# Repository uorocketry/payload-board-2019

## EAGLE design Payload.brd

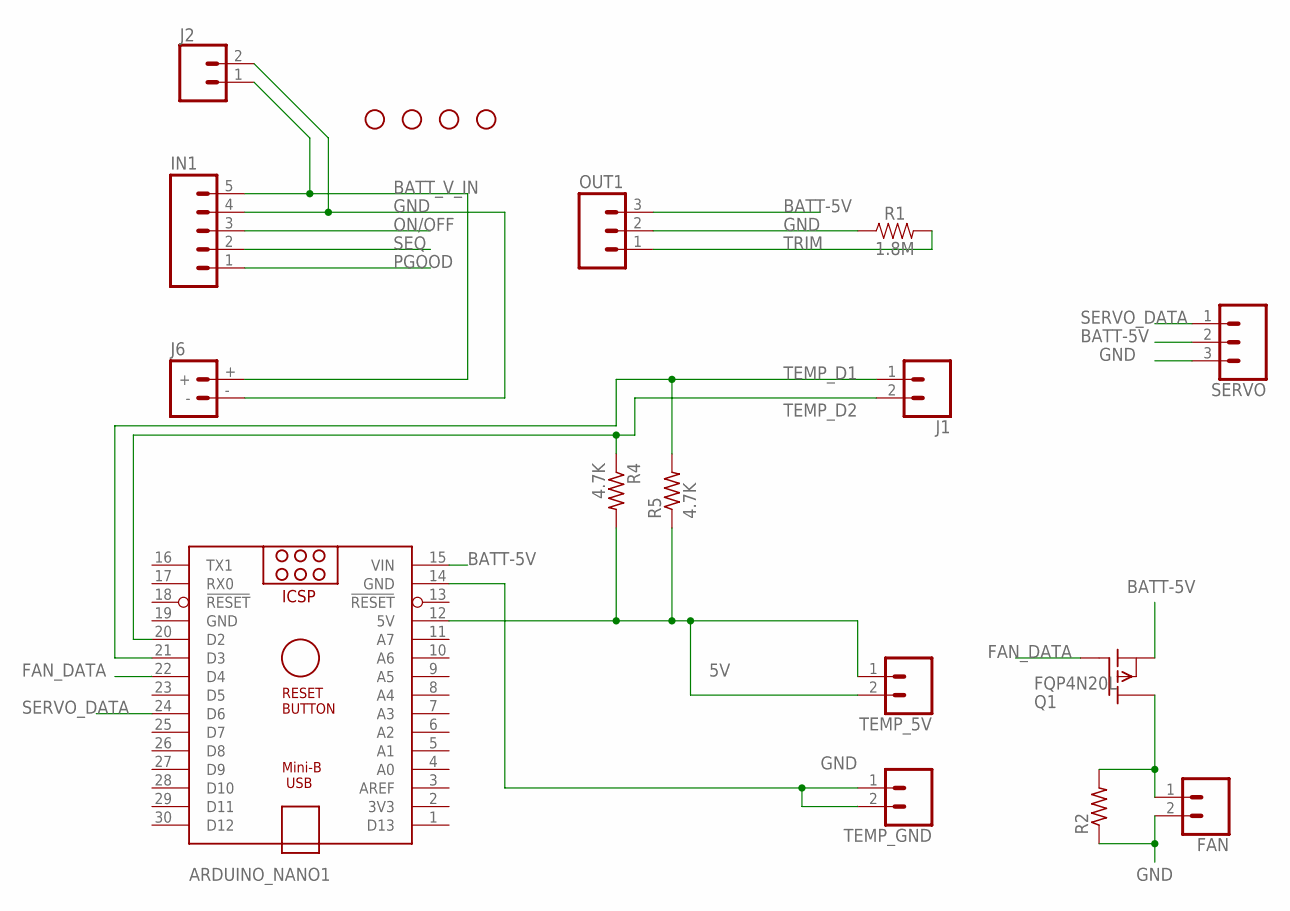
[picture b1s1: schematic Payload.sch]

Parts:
ARDUINO_NANO1: ARDUINO_NANO
FAN: CONN_023.5MM; SCREWTERMINAL-3.5MM-2
IN1: M05PTH; 1X05
J1, J2: CONN_023.5MM; SCREWTERMINAL-3.5MM-2
J6: BATTERY_CONN_DEANS; DEANS
OUT1: M03PTH; 1X03
Q1: FQP4N20L; TO220
R1: 1.8M; 0603
R2: R-US_0207/10; 0207/10
R4, R5: 4.7K; 0207/10
SERVO: CONN_03; 1X03
TEMP_5V: CONN_023.5MM; SCREWTERMINAL-3.5MM-2
TEMP_GND: CONN_023.5MM; SCREWTERMINAL-3.5MM-2
U$2, U$6, U$7, U$8: STAND-OFF

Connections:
5V: ARDUINO_NANO1.12 (5V), R4.2, R5.1, TEMP_5V.1, TEMP_5V.2
BATT-5V: ARDUINO_NANO1.15 (VIN), OUT1.3, Q1.3 (S), SERVO.2
BATT_V_IN: IN1.5, J2.1, J6.+
FAN_DATA: ARDUINO_NANO1.22 (D4), Q1.1 (G)
GND: ARDUINO_NANO1.14 (GND), ARDUINO_NANO1.19 (GND), FAN.2, IN1.4, J2.2, J6.-, OUT1.2, R1.1, R2.1, SERVO.3, TEMP_GND.1, TEMP_GND.2
unnamed: FAN.1, Q1.2 (D), R2.2
ON/OFF: IN1.3
PGOOD: IN1.1
SEQ: IN1.2
SERVO_DATA: ARDUINO_NANO1.24 (D6), SERVO.1
TEMP_D1: ARDUINO_NANO1.21 (D3), J1.1, R5.2
TEMP_D2: ARDUINO_NANO1.20 (D2), J1.2, R4.1
TRIM: OUT1.1, R1.2

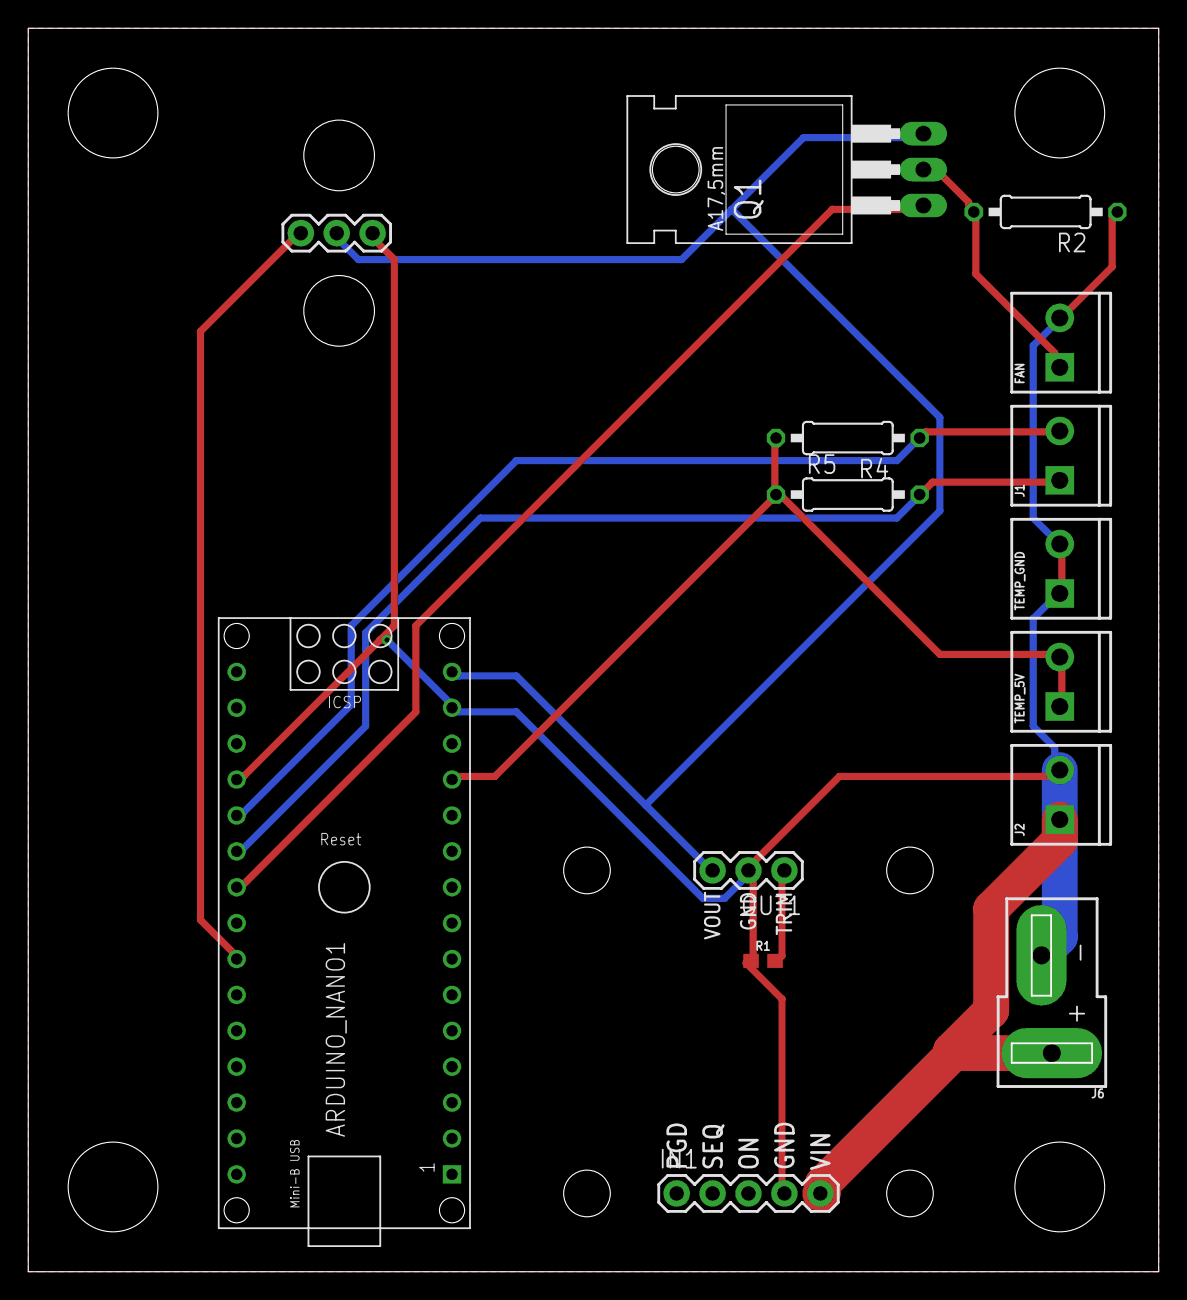
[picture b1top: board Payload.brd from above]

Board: 2 copper layers, 80.0 x 88.0 mm, 19 parts (0 on the bottom side), 10 nets.

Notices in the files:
parts and their libraries:
SparkFun-Connectors: Licensing: Creative Commons ShareAlike 4.0 International - https://creativecommons.org/licenses/by-sa/4.0
